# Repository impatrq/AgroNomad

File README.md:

<div align="center">
    
# [AgroNomad](https://linktr.ee/agronomad2026)

&nbsp;

| Página web | Linkedin | Instagram | Tiktok |
|------------|-------|-----------|---------|
|[AgroNomad Page](https://agro-nomad-page.vercel.app)|[AgroNomad](https://www.linkedin.com/company/145449198)|[@proyecto.agronomad](https://www.instagram.com/proyecto.agronomad/)|[@proyecto.agronomad](https://www.tiktok.com/@proyecto.agronomad)|

### MONITOREO INTELIGENTE DE GANADO 

AgroNomad es un sistema de monitoreo inteligente de ganado que combina collares smart, sensores, posicionamiento GPS y comunicación LoRa para obtener información de los animales directamente desde el campo.

El sistema está compuesto por collares inteligentes, una estación de recepción fija y una interfaz de usuario que permite visualizar y gestionar la información obtenida.

---

## Objetivo

Desarrollar un sistema IoT que permita realizar el seguimiento remoto del ganado, obteniendo información sobre su ubicación, movimiento y diferentes parámetros del animal, y centralizando estos datos en una estación de control.

---

## Componentes del Proyecto  

### AgroNeck

Collar inteligente colocado en el animal.

Se encarga de adquirir y procesar la información proveniente de los sensores y transmitirla mediante LoRa hacia el AgroBot.

### AgroBot

Estación de recepción fija del sistema.

Recibe la información enviada por los AgroNeck y funciona como centro de control para los animales monitoreados.

### AgroServer

Interfaz de usuario del sistema.

Permite visualizar y gestionar la información recibida desde los AgroNeck a través del AgroBot.

---

## Estructura del Proyecto  
**docs/** Documentación e Informes del Proyecto  
**firmware/** Código de los Microcontroladores  
**hardware/** Esquemáticos y PCB  
**mechanical/** Diseños 3D  
**web/** Landing Page del Proyecto  

---

### AgroNeck  

### AgroBot

---

## Equipo AgroNomad

<div align="center">
  
</div>

<br />

| Integrante | Rol | LinkedIn |
|------------|-----|----------|
| **Della Torre, Joaquín** | Diseño de placas electrónicas, montaje del AgroBot y desarrollo del AgroServer y Base de Datos. | [linkedin.com/in/joaquin-della-torre](https://www.linkedin.com/in/joaquin-della-torre/) |
| **Gonzalez Camiscia, Santiago** | Programación del AgroNeck, sistemas, optimización y gestión de energía con ESP32. | [linkedin.com/in/santiago-gonzalez](https://www.linkedin.com/in/santiago-gonzalez-a80209353/) |
| **Romero Dominguez, Braulio** | Diseño físico, desarrollo e integración del hardware y firmware y documentación. | [linkedin.com/in/braulio-romero-dominguez](www.linkedin.com/in/braulio-romero-dominguez-9a4729419) |
| **Villegas Gonzalez, Alejandro** | Desarrollo Web y de Interfaces. Programación e integración de datos. | [linkedin.com/in/alejandro-villegas-gonzalez](https://www.linkedin.com/in/alejandro-villegas-gonzalez-748a94432/) |

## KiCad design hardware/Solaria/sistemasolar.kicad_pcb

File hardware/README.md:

# hardware
Diseños electrónicos del ecosistema AgroNomad desarrollados en KiCad.

---

### Estructura del Proyecto
**AgroBot/** Estación de recepción fija con Raspberry Pi Zero 2W  
**Cortex/** Placa principal del AgroNeck con ESP32  
**LoraShield/** Módulo adaptador de Lora SMD a THT  
**MLXModule/** Placa de soporte del Sensor de Temperatura MLX90614  
**Solaria/** Placa de Alimentación Solar y Gestión Energética  

---

## AgroBot

## Cortex

## LoraShield

## MLXModule

## Solaria

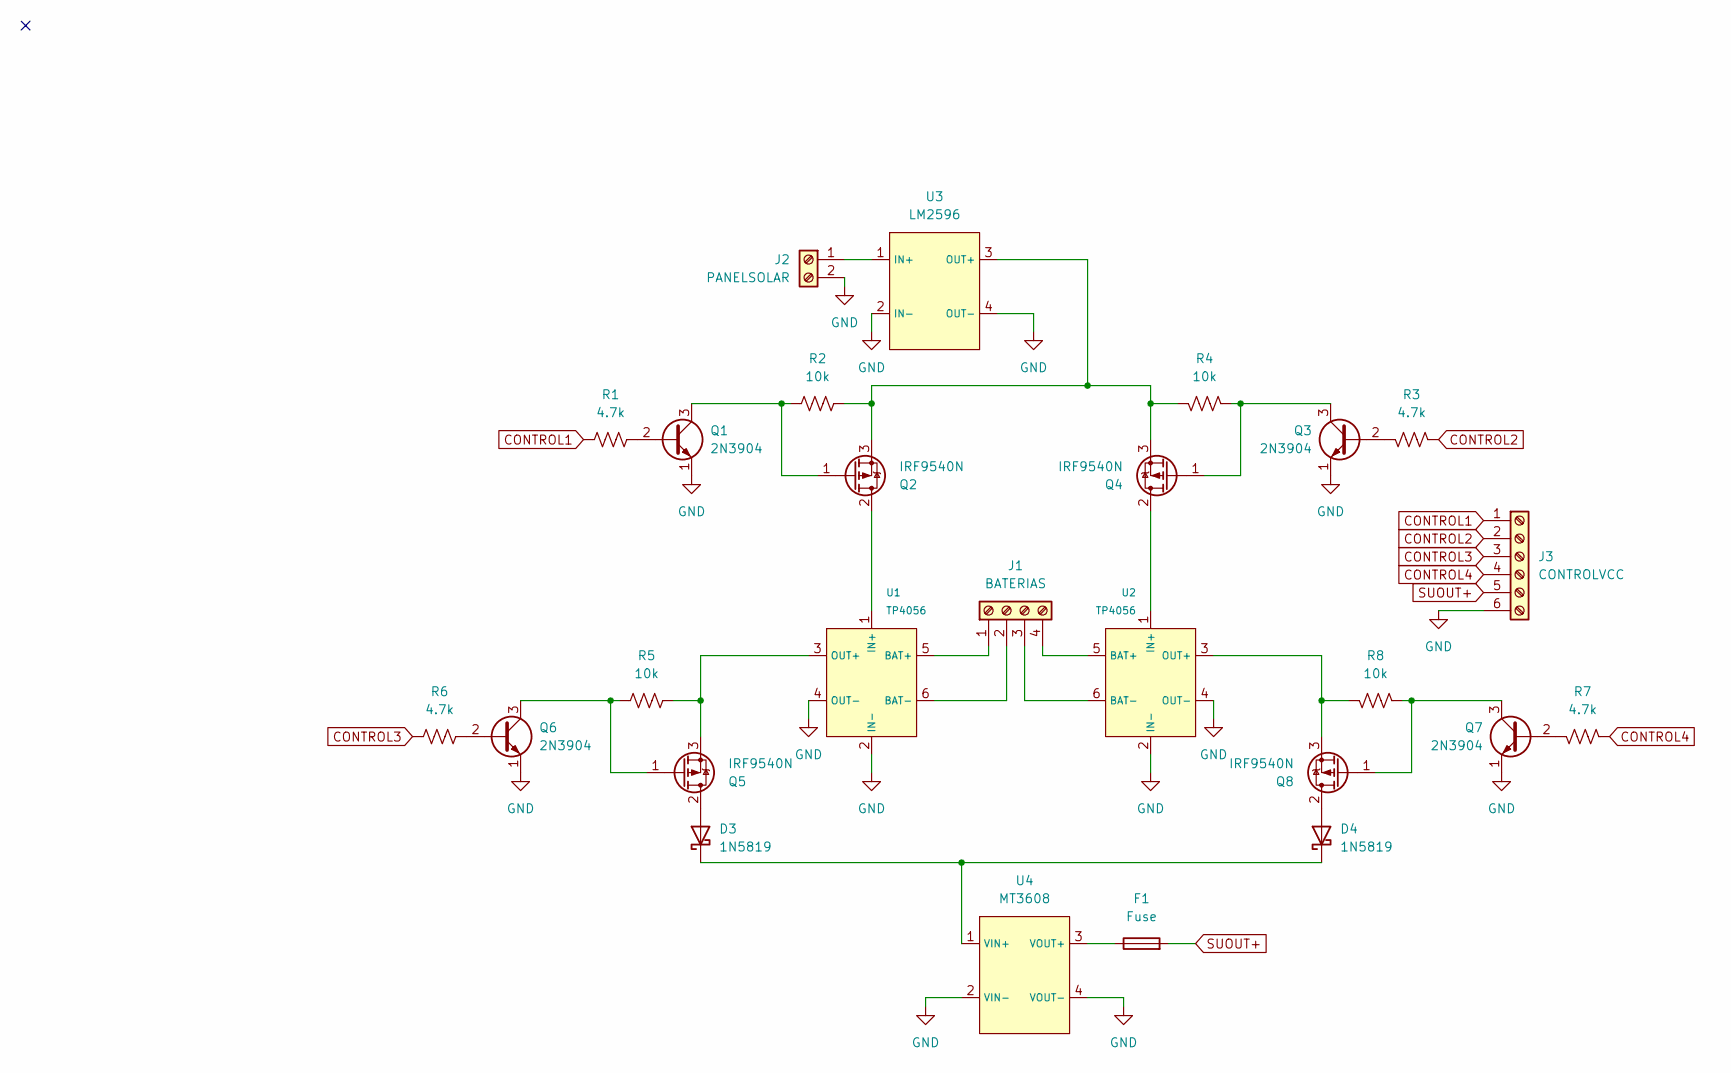
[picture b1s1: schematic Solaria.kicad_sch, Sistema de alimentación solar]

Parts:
D3, D4: 1N5819; D_DO-41_SOD81_P10.16mm_Horizontal
F1: Fuse; Fuseholder_Clip-5x20mm_Littelfuse_445-030_Inline_P20.50x5.2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
J1: BATERIAS; TerminalBlock_MaiXu_MX126-5.0-04P_1x04_P5.00mm
J2: PANELSOLAR; TerminalBlock_MaiXu_MX126-5.0-02P_1x02_P5.00mm
J3: CONTROLVCC; TerminalBlock_MaiXu_MX126-5.0-06P_1x06_P5.00mm
Q1, Q3, Q6, Q7: 2N3904; TO-92_Inline
Q2, Q4, Q5, Q8: IRF9540N; TO-220-3_Vertical
R1, R3, R6, R7: 4.7k; R_Axial_DIN0204_L3.6mm_D1.6mm_P7.62mm_Horizontal
R2, R4, R5, R8: 10k; R_Axial_DIN0204_L3.6mm_D1.6mm_P7.62mm_Horizontal
U1, U2: TP4056
U3: LM2596
U4: MT3608

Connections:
CONTROL1: J3.1, R1.1
CONTROL2: J3.2, R3.1
CONTROL3: J3.3, R6.1
CONTROL4: J3.4, R7.1
GND: J2.2, J3.6, Q1.1 (E), Q3.1 (E), Q6.1 (E), Q7.1 (E), U1.2 (IN-), U1.4 (OUT-), U2.2 (IN-), U2.4 (OUT-), U3.2 (IN-), U3.4 (OUT-), U4.2 (VIN-), U4.4 (VOUT-)
unnamed: D3.2 (A), Q5.2 (D)
unnamed: D3.1 (K), D4.1 (K), U4.1 (VIN+)
unnamed: D4.2 (A), Q8.2 (D)
unnamed: J1.1, U1.5 (BAT+)
unnamed: J1.2, U1.6 (BAT-)
unnamed: J1.3, U2.6 (BAT-)
unnamed: J1.4, U2.5 (BAT+)
unnamed: J2.1, U3.1 (IN+)
unnamed: Q1.2 (B), R1.2
unnamed: Q1.3 (C), Q2.1 (G), R2.1
unnamed: Q2.2 (D), U1.1 (IN+)
unnamed: Q2.3 (S), Q4.3 (S), R2.2, R4.2, U3.3 (OUT+)
unnamed: Q3.2 (B), R3.2
unnamed: Q3.3 (C), Q4.1 (G), R4.1
unnamed: Q4.2 (D), U2.1 (IN+)
unnamed: Q5.1 (G), Q6.3 (C), R5.1
unnamed: Q5.3 (S), R5.2, U1.3 (OUT+)
unnamed: Q6.2 (B), R6.2
unnamed: Q7.2 (B), R7.2
unnamed: Q7.3 (C), Q8.1 (G), R8.1
unnamed: Q8.3 (S), R8.2, U2.3 (OUT+)
unnamed: F1.1, U4.3 (VOUT+)
SUOUT+: F1.2, J3.5

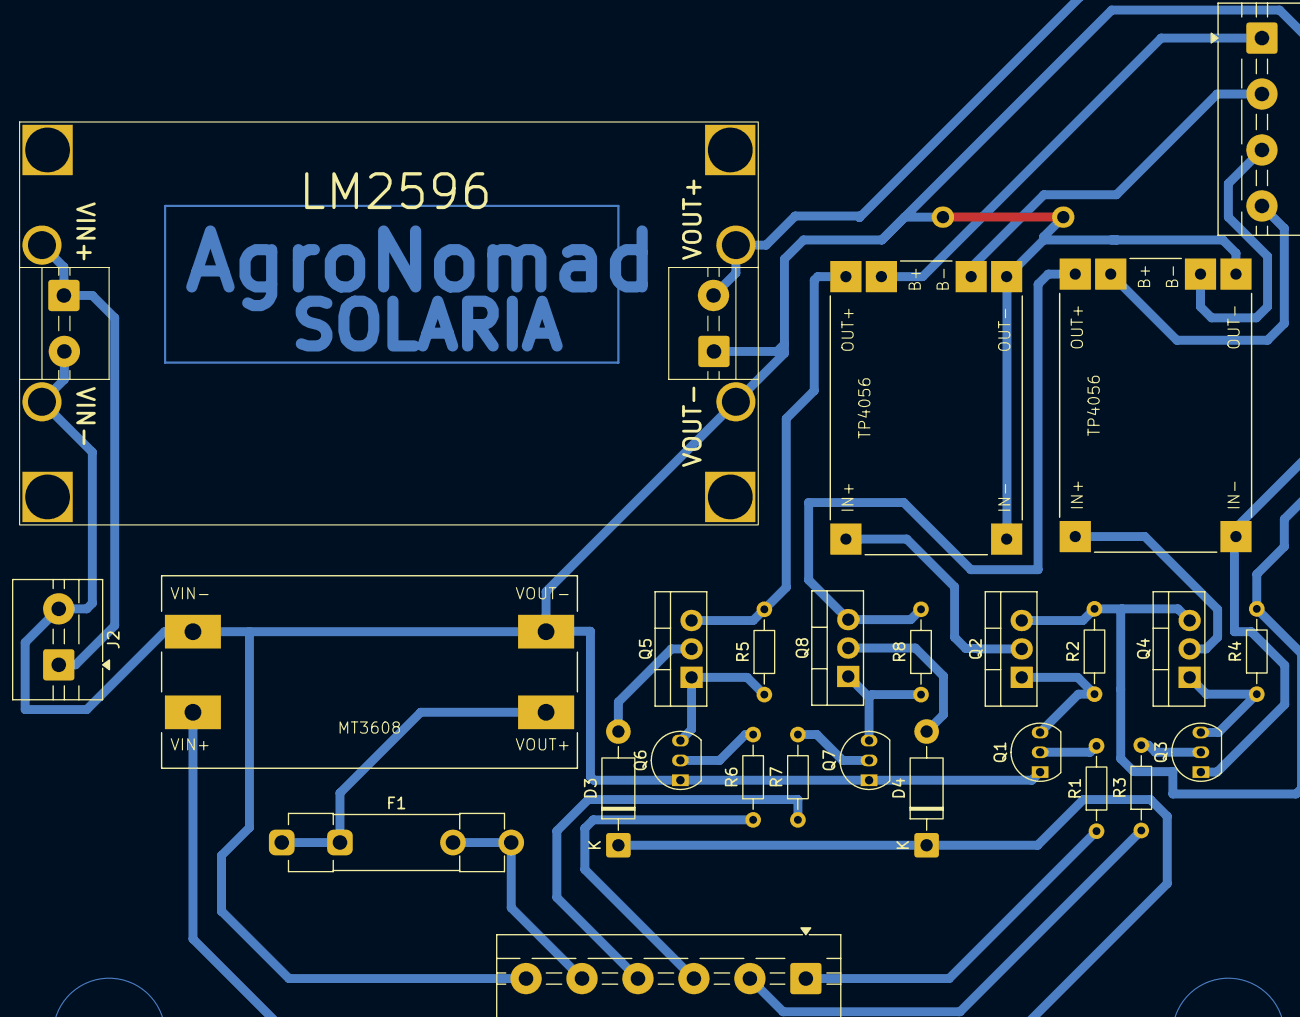
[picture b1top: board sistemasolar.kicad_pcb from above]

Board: 2 copper layers, 26 parts (0 on the bottom side), 28 nets.

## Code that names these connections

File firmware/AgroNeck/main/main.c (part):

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#define SEND_EVERYTIME 1

// CONTROL DE ALIMENTACIÓN - C1+C4 o C2+C3
#define MOSFET1 25 // GPIO del MOSFET CONTROL3
#define MOSFET2 26 // GPIO del MOSFET CONTROL4
#define MOSFET3 32 // GPIO del MOSFET CONTROL1
#define MOSFET4 33 // GPIO del MOSFET CONTROL2

// Mascara de manejo de los 4 pines
#define GPIO_MOSFET_MASK ((1ULL<<MOSFET1) | (1ULL<<MOSFET2) | (1ULL<<MOSFET3) | (1ULL<<MOSFET4))
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
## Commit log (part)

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2026-04-08 Anteproyecto uploaded
2026-04-08 docs readme updated
2026-04-08 created dir for docs
2026-06-03 feat(solaria): proyecto inicial de KiCad de placa de alimentación solar
    esquemático, pcb y modelo 3d de la placa
2026-06-16 added hardware directory with PCB developed until 15/6
